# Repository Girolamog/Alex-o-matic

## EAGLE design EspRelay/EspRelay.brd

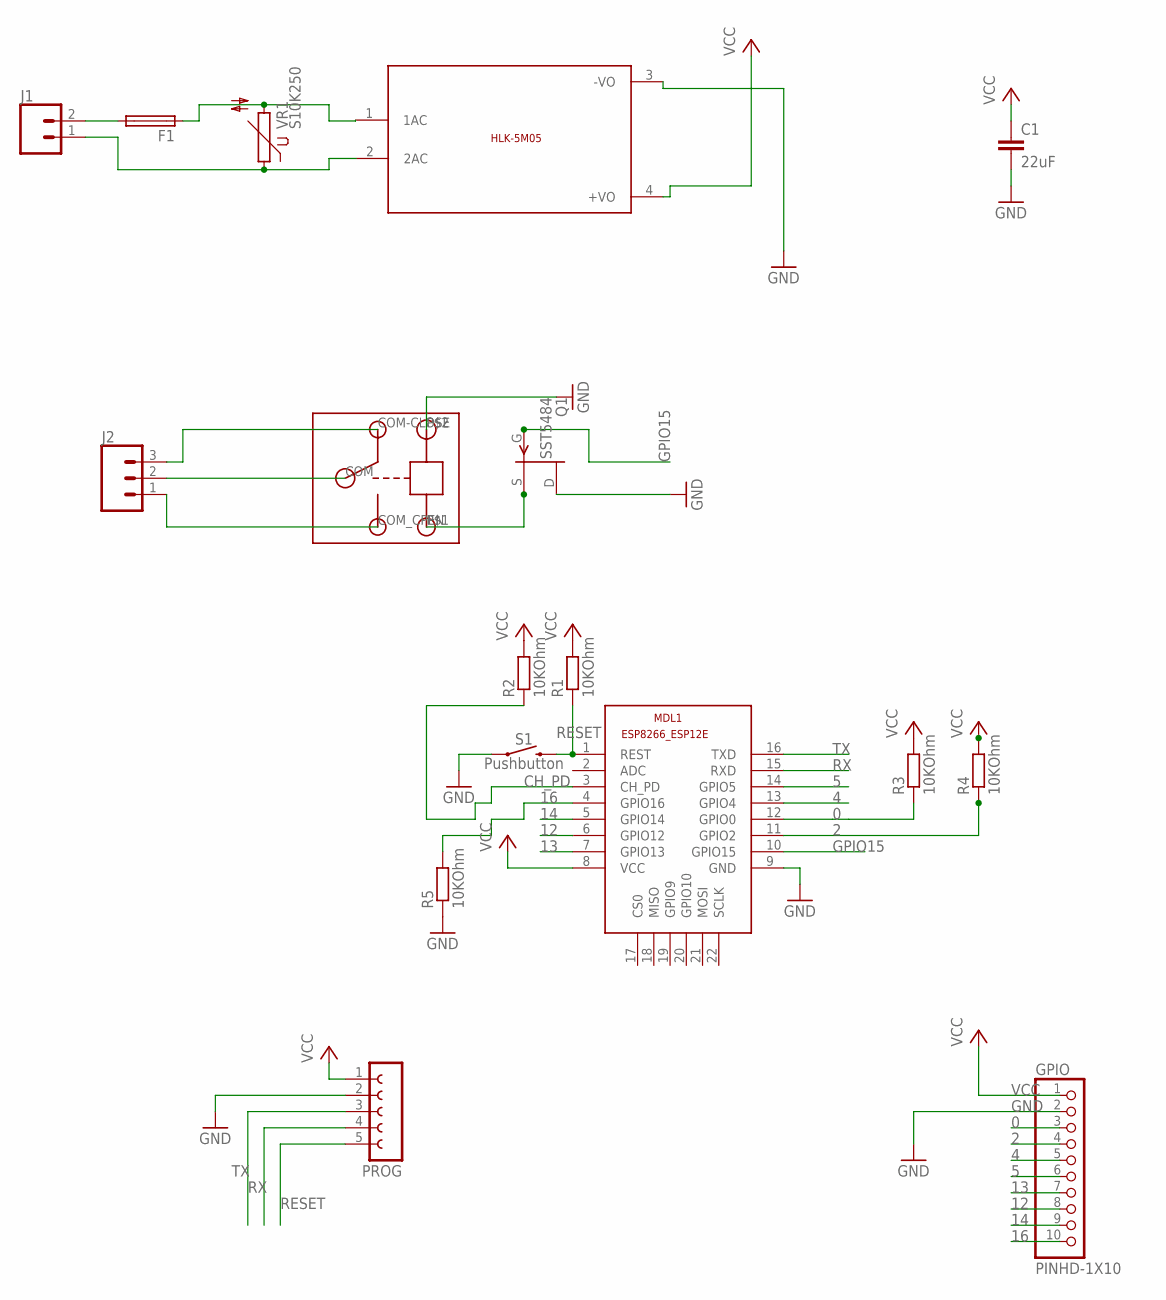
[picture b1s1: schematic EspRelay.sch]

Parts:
C1: 22uF; 0402-CAP
F1: PICOFUSE
GPIO: PINHD-1X10; 1X10-BIG
J1: CONN_025MM; SCREWTERMINAL-5MM-2
J2: CONN_03-SCREW-5MM; SCREWTERMINAL-5MM-3
MDL1: ESP8266-12EESP8266-ESP12E; ESP8266-ESP12E
PROG: FE05-1
Q1: SST5484; SOT23
R1, R2, R3, R4, R5: 10KOhm; R0805
S1: Pushbutton; TACTILE_SWITCH_SMD_6.0X3.5MM
U$1: RELAY
U$2: 5VDC/5W; HLK-5M05
VR1: S10K250

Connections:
0: GPIO.3, MDL1.12 (GPIO0), R3.1
2: GPIO.4, MDL1.11 (GPIO2), R4.1
4: GPIO.5, MDL1.13 (GPIO4)
5: GPIO.6, MDL1.14 (GPIO5)
12: GPIO.8, MDL1.6 (GPIO12)
13: GPIO.7, MDL1.7 (GPIO13)
14: GPIO.9, MDL1.5 (GPIO14)
16: GPIO.10, MDL1.4 (GPIO16), R5.2
CH_PD: MDL1.3 (CH_PD), R2.1
GND: C1.2, GPIO.2, MDL1.9 (GND), PROG.2, Q1.1 (D), R5.1, S1.1, U$1.P$2 (GND), U$2.3 (-VO)
GPIO15: MDL1.10 (GPIO15), Q1.3 (G)
unnamed: Q1.2 (S), U$1.P$1 (IN)
unnamed: J2.1, U$1.COM_CPEN (COM-OPEN)
unnamed: J2.2, U$1.COM
unnamed: J2.3, U$1.COM-CLOSE
unnamed: F1.2, J1.2
unnamed: J1.1, U$2.2 (2AC), VR1.1
unnamed: F1.1, U$2.1 (1AC), VR1.2
RESET: MDL1.1 (REST), PROG.5, R1.1, S1.2
RX: MDL1.15 (RXD), PROG.4
TX: MDL1.16 (TXD), PROG.3
VCC: C1.1, GPIO.1, MDL1.8 (VCC), PROG.1, R1.2, R2.2, R3.2, R4.2, U$2.4 (+VO)

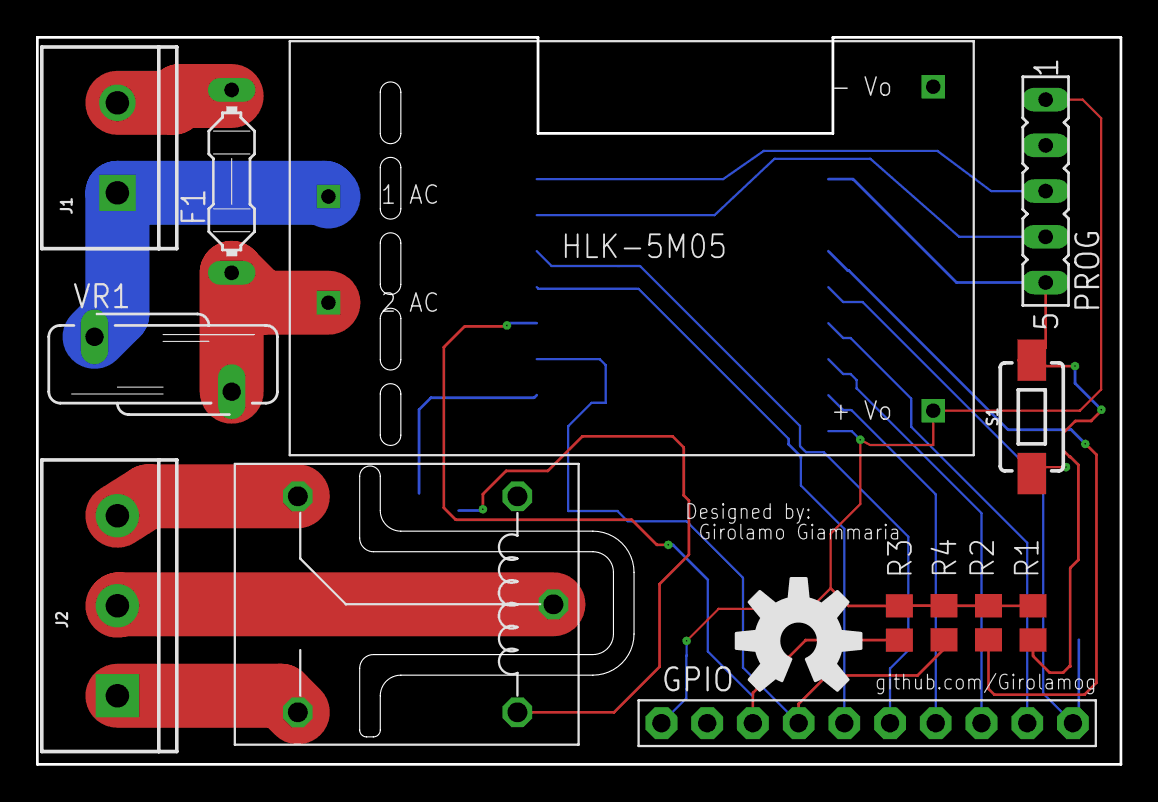
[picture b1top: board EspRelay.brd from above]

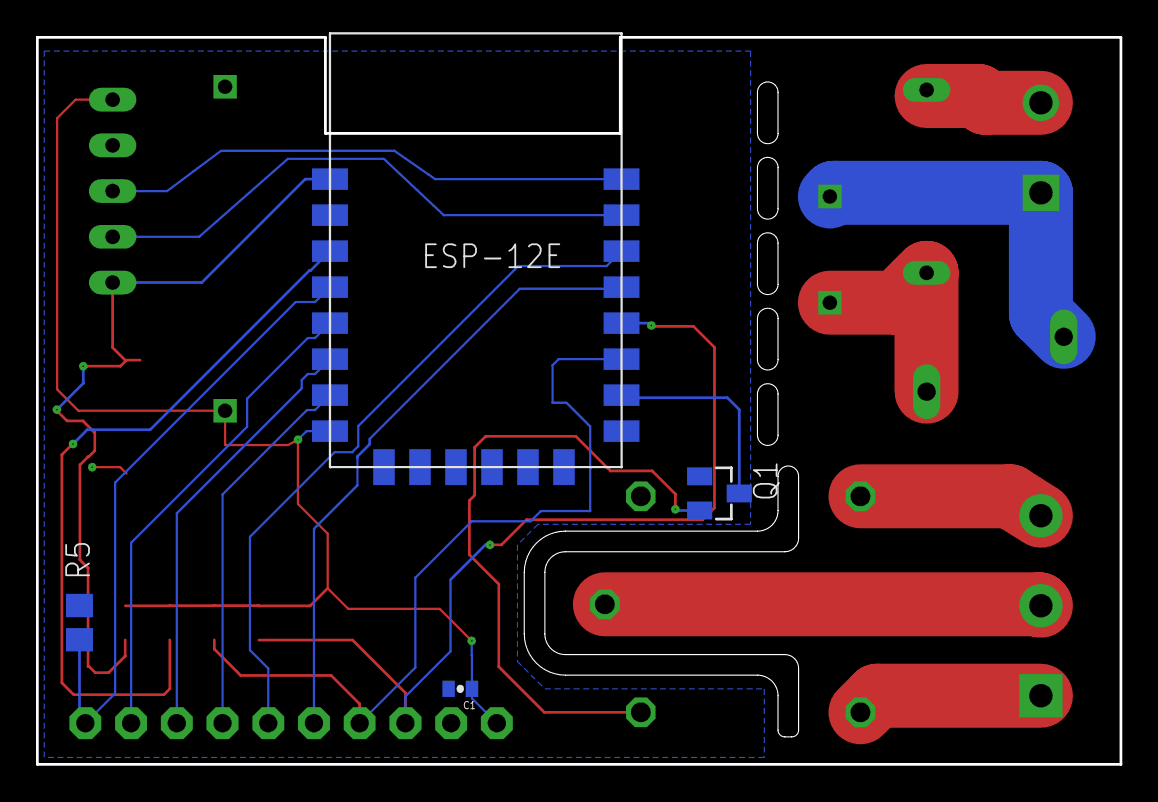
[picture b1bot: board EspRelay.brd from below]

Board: 2 copper layers, 60.2 x 40.4 mm, 18 parts (4 on the bottom side), 22 nets.

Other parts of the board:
U$3: OSHW-LOGO-L

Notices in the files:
parts and their libraries:
SparkFun-Retired: Licensing: Creative Commons ShareAlike 4.0 International - https://creativecommons.org/licenses/by-sa/4.0
